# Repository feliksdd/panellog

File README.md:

# PanelLog

PanelLog misst und schaltet den DC-Ertrag eines einzelnen PV-Moduls. Ein Knoten sitzt zwischen Modul und MPPT-Eingang, versorgt sich aus dem Modul und soll seine Daten per Zigbee an BatteryFlex übertragen. Pro Modul wird ein eigener Knoten eingesetzt; verschiedene MPPT-Eingänge bleiben elektrisch getrennt.

## Funktionen

- Modulspannung, Modulstrom sowie daraus berechnete DC-Leistung und Energie.
- Modultemperatur über einen externen Pt1000; lokale Platinentemperatur über NTC.
- Langsame Ein-/Ausschaltung des Modulstroms über einen Low-Side-MOSFET mit Spannungsrückmeldung.
- Optional ein kabelgebundener [POA-Sensor](https://github.com/feliksdd/poa-sensor) zur Einstrahlungsmessung, versorgt über 3,3 V und angeschlossen an einen separaten I²C-Bus.

## Aufbau

| Baugruppe | Ausführung |
|---|---|
| Controller / Funk | ESP32-C6-WROOM-1-N4 |
| Strom und Spannung | INA237AIDGSR, HoVB4026-Vierleiter-Shunt mit 1 mΩ |
| Modulschalter | IPT015N10N5, passiv eingeschaltet, aktiv ausgeschaltet |
| Versorgung | LM5163DDAR, direkt vom Modul auf nominal 3,3 V, bis 500 mA |
| Temperatur | Externer M222 Pt1000 Klasse A; interner 10-kΩ-NTC |
| Mechanik | Vierlagige Platine 118 × 90 × 1,6 mm, Kradex Z74JH ABS |

Der PV-Pluspol ist durchverbunden. Der Rückstrom fließt vom MPPT-Minuspol über Shunt und Q1 zum Modul-Minuspol. Die Elektronik liegt auf Modul-Minus und bleibt bei ausgeschaltetem Q1 versorgt.

Der Spannungsentwurf umfasst ein einzelnes Modul bis 60 V DC; die Versorgung startet typisch bei etwa 9 V. 15 A ist der ursprüngliche Strom-Auslegungspunkt, 20 A ein thermischer Betrachtungsfall. Daraus folgt keine gemessene Dauerstromfreigabe. Kalte Leerlaufspannung und Schaltspitzen der konkreten Modul-/MPPT-Kombination müssen innerhalb der Bauteilgrenzen bleiben. Q1 dient der Ertragsregelung; eine sichere Trennstelle entsteht dadurch nicht.

## Dokumentation

| Inhalt | Datei |
|---|---|
| Schaltungsfunktion und Bauteilwerte | [Schaltung](docs/schaltung.md) |
| Berechnungen, Messbereiche und Genauigkeit | [Auslegung](docs/auslegung.md) |
| Verdrahtung, Montage, Kalibrierung und Betrieb | [Anwendung](docs/anwendung.md) |
| Gehäuse, Lochbild und 3D-Einbindung | [Gehäuse](docs/gehaeuse.md) |
| POA-Kabel und Bestückungsvarianten | [POA-Schnittstelle](docs/poa_schnittstelle.md) |
| KiCad-Projekt und Lagenaufbau | [Hardware](hardware/README.md) |
| Stückliste und Fertigungsunterlagen | [Bestückung](bom/README.md) |
| Pinbelegung und Softwareumfang | [Firmware](firmware/README.md) |
| Vorhandene Gehäuse- und Bauteilmodelle | [3D-Modelle](hardware/3dmodels/README.md) |

Schaltplan und PCB in [hardware/kicad](hardware/kicad/) definieren die Hardware. Das Repository enthält einen POA-Treiberbaustein, aber noch keine vollständige PanelLog-Firmware mit Zigbee-/BatteryFlex-Anbindung.

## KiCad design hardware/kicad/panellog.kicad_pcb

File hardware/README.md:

# Hardware

Das KiCad-10-Projekt liegt in [kicad/panellog.kicad_pro](kicad/panellog.kicad_pro). [Schaltplan](kicad/panellog.kicad_sch) und [PCB](kicad/panellog.kicad_pcb) sind die verbindlichen Konstruktionsdateien. Projektbibliotheken sind über `sym-lib-table` und `fp-lib-table` eingebunden.

| Verzeichnis | Inhalt |
|---|---|
| `kicad/` | Native Schaltung, Layout und Projekteinstellungen |
| `kicad/production/` | Gerber-/Bohrarchiv, BOM, Positionen und IPC-Netzliste |
| `symbols/` | Projektspezifische Symbole |
| `footprints/PanelLog.pretty/` | Projekt-Footprints |
| `3dmodels/` | Bauteil-/Gehäusemodelle und Lizenzen |
| `mechanical/` | Kradex-Gehäusegeometrie |

## Platine

118 × 90 × 1,6 mm, vier Kupferlagen. Der Umriss liegt in KiCad bei X = 81…199 mm und Y = 44,5…134,5 mm. Vorhandene Befestigungslöcher: H1, H3, H4; siehe [Gehäuse und Montage](../docs/gehaeuse.md). Unterteil und Deckel sind als 3D-Modelle an H1 eingebunden.

| Lage | Funktion |
|---|---|
| F.Cu | Bauteile, Versorgung, lokale Signale und Leistungskupfer |
| In1.Cu | GND-Bezug mit getrennten Leistungskupferbereichen |
| In2.Cu | Signalrouting und Leistungskupferbereiche |
| B.Cu | GND und Leistungskupferbereiche |

VDC, MPPT_MINUS, SHUNT_RETURN und GND führen den Modulstrom über getrennte Kupferbereiche mit Durchkontaktierungen. Die Kelvin-Leitungen gehören ausschließlich an die Sense-Anschlüsse des Shunts. Versorgungs-Schaltknoten, Q1-Gate und externe Digitalsignale benötigen Abstand zu diesen Messleitungen. Antennen-, Schrauben- und Spulensperrflächen sind beim Bearbeiten beizubehalten. Kupfergewicht und thermischer Betriebsstrom sind zusätzlich zur Lagenzahl bei der Fertigung festzulegen.

## Bearbeitung und Fertigung

KiCad 10 mit Standardbibliotheken und den lokalen Bibliothekstabellen verwenden. Nach Hardwareänderungen Zonen neu füllen, ERC/DRC mit Schaltplanabgleich ausführen und Fertigungsausgaben neu erzeugen. Die gespeicherten Ausgaben entsprechen keinem automatisch fortgeschriebenen Live-Export.

[Schaltung](../docs/schaltung.md), [Auslegung](../docs/auslegung.md), [Bestückung](../bom/README.md), [3D-Modelle](3dmodels/README.md).

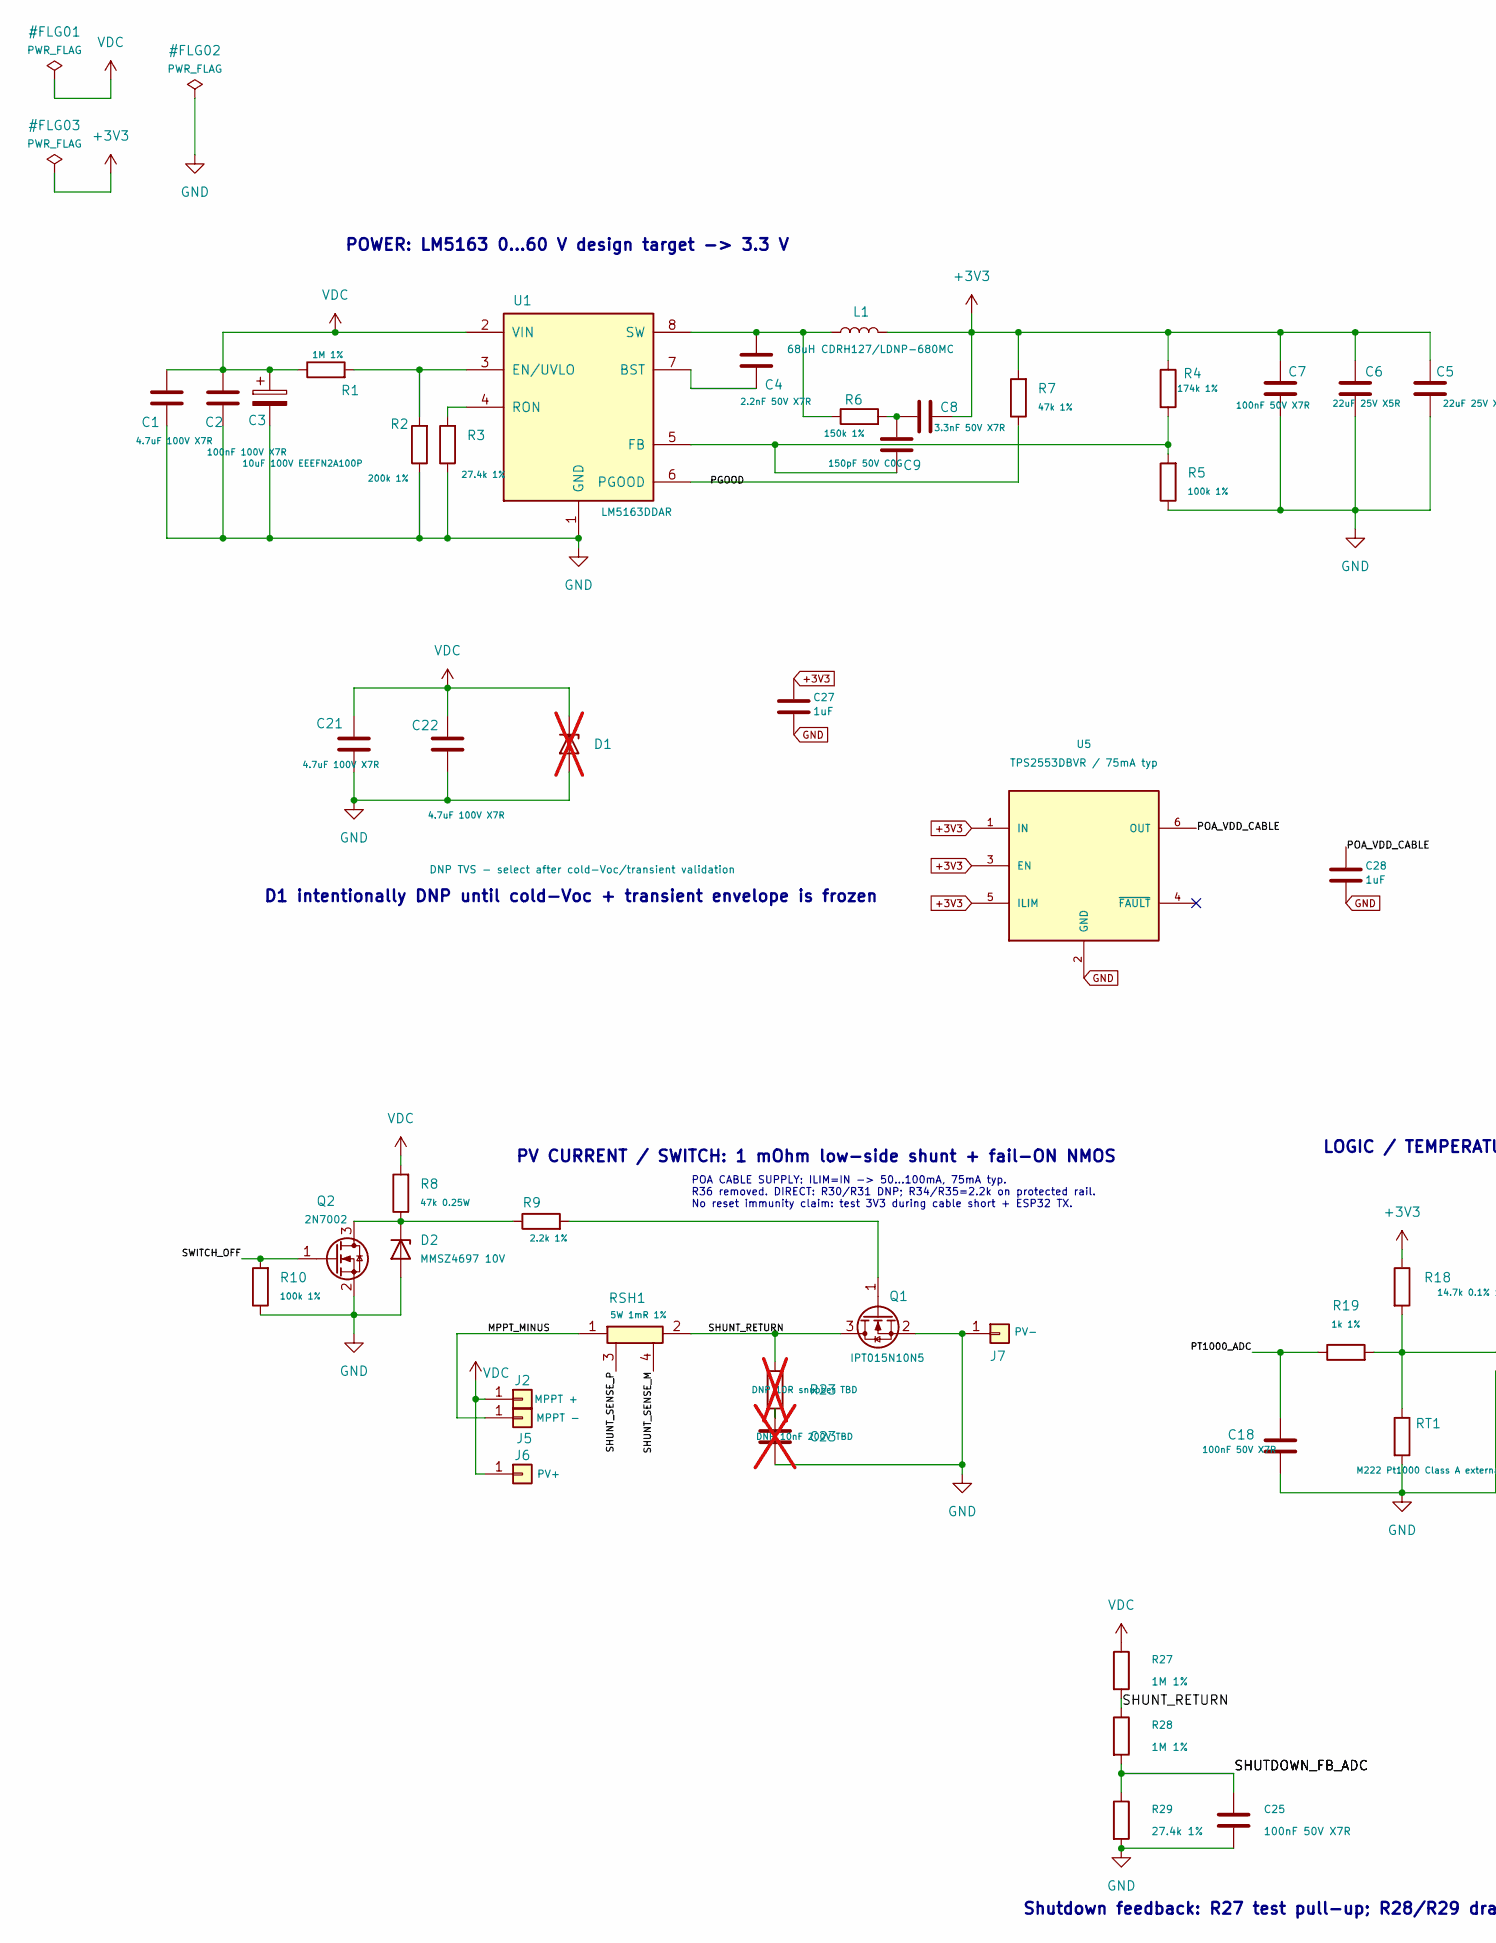
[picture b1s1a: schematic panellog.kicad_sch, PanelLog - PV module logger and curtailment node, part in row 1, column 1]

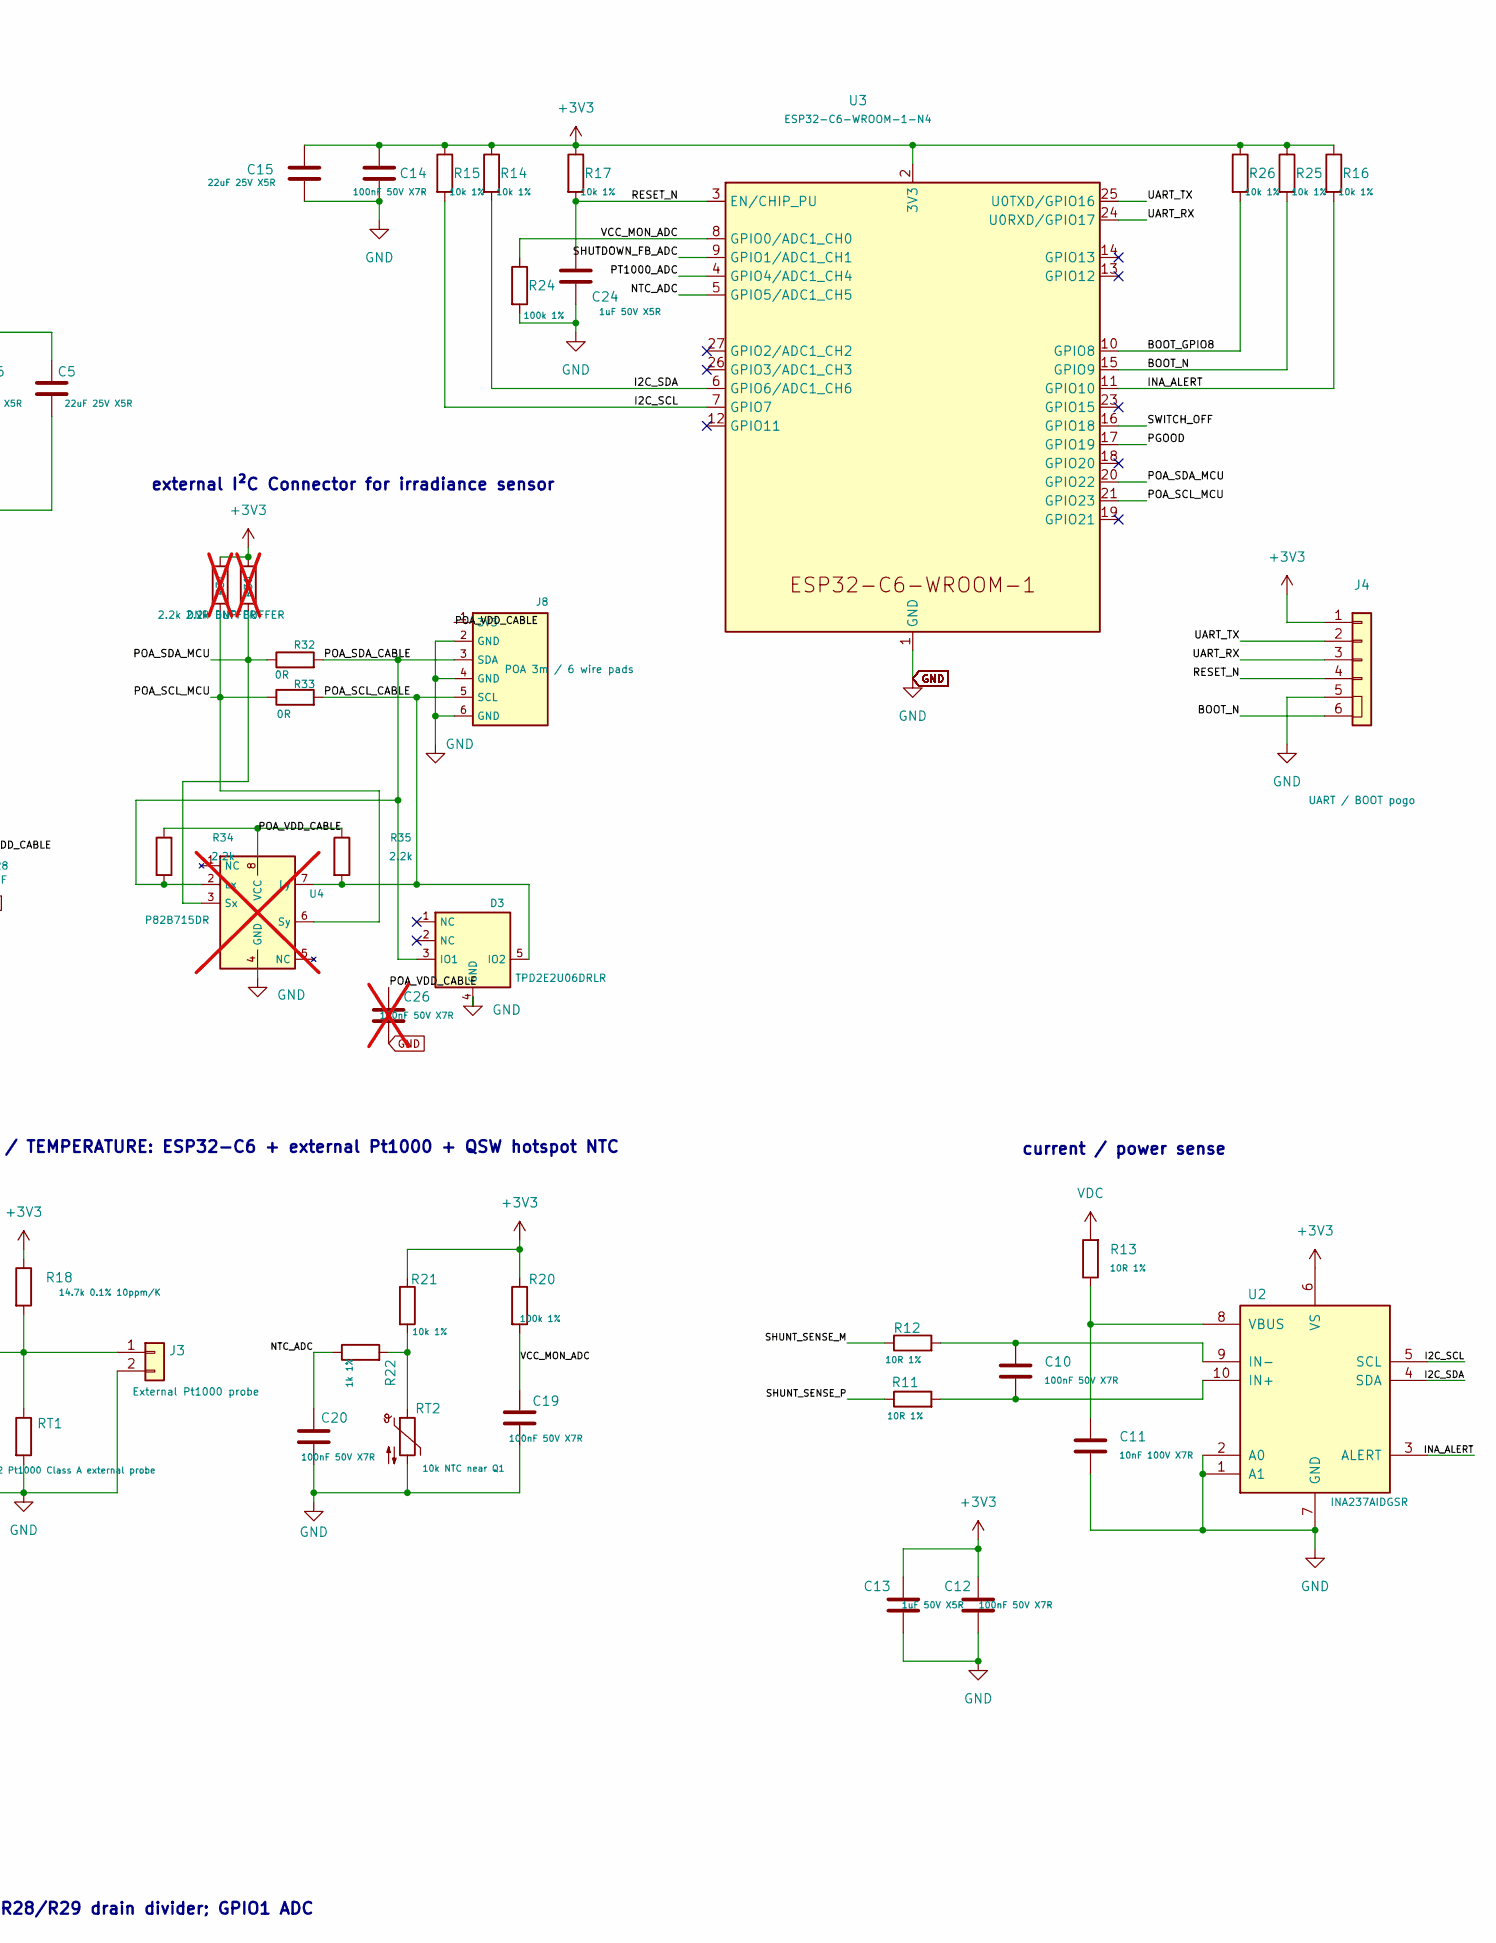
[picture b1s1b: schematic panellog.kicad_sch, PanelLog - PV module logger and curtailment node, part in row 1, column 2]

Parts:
C1, C21, C22: 4.7uF 100V X7R; C_1210_3225Metric; MPN 1210B475K101NT; LCSC C7500895
C2: 100nF 100V X7R; C_0805_2012Metric; MPN CL21B104KCFNNNE; LCSC C28233
C3: 10uF 100V EEEFN2A100P; Panasonic_F_8x10p2; MPN EEEFN2A100P; LCSC C494873
C4: 2.2nF 50V X7R; C_0603_1608Metric; MPN 0603B222K500NT; LCSC C1604
C5, C6, C15: 22uF 25V X5R; C_0805_2012Metric; MPN GRM21BR61E226ME44L; LCSC C86816
C7, C10, C12, C14, C18, C19, C20, C25: 100nF 50V X7R; C_0603_1608Metric; MPN CC0603KRX7R9BB104; LCSC C14663
C8: 3.3nF 50V X7R; C_0603_1608Metric; MPN CL10B332KB8NNNC; LCSC C1613
C9: 150pF 50V C0G; C_0603_1608Metric; MPN CL10C151JB8NNNC; LCSC C37298
C11: 10nF 100V X7R; C_0603_1608Metric; MPN CC0603KRX7R0BB103; LCSC C107059
C13, C24: 1uF 50V X5R; C_0603_1608Metric; MPN CL10A105KB8NNNC; LCSC C15849
C23: DNP 10nF 200V TBD; C_1206_3216Metric; not fitted
C26: 100nF 50V X7R; C_0603_1608Metric; MPN CL10B104KB8NNNC; LCSC C1591; not fitted
C27, C28: 1uF; C_0603_1608Metric; MPN CL10B105KP8NNNC; LCSC C15849
D1: DNP TVS - select after cold-Voc/transient validat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; D_SMB; not fitted
D2: MMSZ4697 10V; D_SOD-123; MPN MMSZ4697; LCSC C2910058
D3: TPD2E2U06DRLR; SOT-553; MPN TPD2E2U06DRLR; LCSC C1972959
J2: MPPT +; PV_MC4_Pigtail_2x2p8_DRAFT
J3: External Pt1000 probe; Pt1000_Cable_2pin_DRAFT
J4: UART / BOOT pogo; UART_BOOT_1x06_Pogo
J5: MPPT -; PV_MC4_Pigtail_2x2p8_DRAFT
J6: PV+; PV_MC4_Pigtail_2x2p8_DRAFT
J7: PV-; PV_MC4_Pigtail_2x2p8_DRAFT
J8: POA 3m / 6 wire pads; POA_Cable_6pad
L1: 68uH CDRH127/LDNP-680MC; Sumida_CDRH127_LD_68uH; MPN CDRH127/LDNP-680MC; LCSC C2452974
Q1: IPT015N10N5; IPT015N10N5_TOLL; MPN 2N7002; LCSC C8545
Q2: 2N7002; SOT-23; MPN 2N7002; LCSC C8545
R1: 1M 1%; R_0603_1608Metric; MPN 0603WAF1004T5E; LCSC C22935
R2: 200k 1%; R_0603_1608Metric; MPN 0603WAF2003T5E; LCSC C25811
R3, R29: 27.4k 1%; R_0603_1608Metric; MPN 0603WAF2742T5E; LCSC C22964
R4: 174k 1%; R_0603_1608Metric; MPN 0603WAF1743T5E; LCSC C22890
R5, R10, R20, R24: 100k 1%; R_0603_1608Metric; MPN 0603WAF1003T5E; LCSC C25803
R6: 150k 1%; R_0603_1608Metric; MPN 0603WAF1503T5E; LCSC C22807
R7: 47k 1%; R_0603_1608Metric; MPN 0603WAF4702T5E; LCSC C25819
R8: 47k 0.25W; R_1206_3216Metric; MPN SCR1206F47K; LCSC C5140109
R9: 2.2k 1%; R_0603_1608Metric; MPN 0603WAF2201T5E; LCSC C4190
R11, R12, R13: 10R 1%; R_0603_1608Metric; MPN 0603WAF100JT5E; LCSC C22859
R14, R15, R16, R17, R21, R25, R26: 10k 1%; R_0603_1608Metric; MPN 0603WAF1002T5E; LCSC C25804
R18: 14.7k 0.1% 10ppm/K; R_0603_1608Metric; MPN PTFR0603B14K7N9; LCSC C19680002
R19, R22: 1k 1%; R_0603_1608Metric; MPN 0603WAF1001T5E; LCSC C21190
R23: DNP 10R snubber TBD; R_1206_3216Metric; not fitted
R27, R28: 1M 1%; R_1206_3216Metric; MPN 1206W4F1004T5E; LCSC C17927
R30, R31: 2.2k DNP BUFFER; R_0603_1608Metric; MPN 0603WAF2201T5E; LCSC C4190; not fitted
R32, R33: 0R; R_0603_1608Metric; MPN 0603WAF0000T5E; LCSC C21189
R34, R35: 2.2k; R_0603_1608Metric; MPN 0603WAF2201T5E; LCSC C4190
RSH1: 5W 1mR 1%; HOVB4026_R001_Kelvin; MPN HOVB4026-5W-1mR-1%; LCSC C481535
RT1: M222 Pt1000 Class A external probe; MPN 32208572; LCSC C17472362
RT2: 10k NTC near Q1; R_0603_1608Metric; MPN NTCG163JF103FT1S; LCSC C406719
U1: LM5163DDAR; LM5164_DDA; MPN LM5163DDAR; LCSC C2873264
U2: INA237AIDGSR; INA237_DGS10; MPN INA237AIDGSR; LCSC C2864837
U3: ESP32-C6-WROOM-1-N4; ESP32_C6_WROOM_1; MPN ESP32-C6-WROOM-1-N4; LCSC C6034714
U4: P82B715DR; SOIC-8_3.9x4.9mm_P1.27mm; MPN P82B715DR; LCSC C2649394; not fitted
U5: TPS2553DBVR / 75mA typ; SOT-23-6; MPN TPS2553DBVR; LCSC C55266

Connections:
/BOOT_GPIO8: R26.2, U3.10 (GPIO8)
/BOOT_N: J4.6, R25.2, U3.15 (GPIO9)
/I2C_SCL: R15.2, U2.5 (SCL), U3.7 (GPIO7)
/I2C_SDA: R14.2, U2.4 (SDA), U3.6 (GPIO6/ADC1_CH6)
/INA_ALERT: R16.2, U2.3 (ALERT), U3.11 (GPIO10)
/MPPT_MINUS: J5.1 (Pin_1_1), RSH1.1
/NTC_ADC: C20.1, R22.1, U3.5 (GPIO5/ADC1_CH5)
/PGOOD: R7.1, U1.6 (PGOOD), U3.17 (GPIO19)
/POA_SCL_CABLE: D3.5 (IO2), J8.5 (SCL), R33.2, R35.2, U4.7 (Ly)
/POA_SCL_MCU: R31.2, R33.1, U3.21 (GPIO23), U4.6 (Sy)
/POA_SDA_CABLE: D3.3 (IO1), J8.3 (SDA), R32.2, R34.2, U4.2 (Lx)
/POA_SDA_MCU: R30.2, R32.1, U3.20 (GPIO22), U4.3 (Sx)
/PT1000_ADC: C18.1, R19.1, U3.4 (GPIO4/ADC1_CH4)
/RESET_N: C24.1, J4.4, R17.2, U3.3 (EN/CHIP_PU)
/SHUNT_RETURN: Q1.3 (D), R23.1, R27.2, R28.1, RSH1.2
/SHUNT_SENSE_M: R12.1, RSH1.4
/SHUNT_SENSE_P: R11.1, RSH1.3
/SHUTDOWN_FB_ADC: C25.1, R28.2, R29.1, U3.9 (GPIO1/ADC1_CH1)
/SWITCH_OFF: Q2.1 (G), R10.2, U3.16 (GPIO18)
/UART_RX: J4.3, U3.24 (U0RXD/GPIO17)
/UART_TX: J4.2, U3.25 (U0TXD/GPIO16)
/VCC_MON_ADC: C19.1, R20.2, R24.1, U3.8 (GPIO0/ADC1_CH0)
GND: C1.2, C2.2, C3.2, C5.2, C6.2, C7.2, C11.1, C12.2, C13.2, C14.1, C15.2, C18.2, C19.2, C20.2, C21.2, C22.2, C23.2, C24.2, C25.2, C26.2, C27.2, C28.2, D1.2 (A), D2.2 (A), D3.4 (GND), J3.2, J4.5, J7.1 (Pin_1_1), J8.2 (GND), J8.4 (GND), J8.6 (GND), Q1.2 (S), Q2.2 (S), R2.1, R3.1, R5.1, R10.1, R24.2, R29.2, RT1.2, RT2.2, U1.1 (GND), U1.9 (EP), U2.1 (A1), U2.2 (A0), U2.7 (GND), U3.1 (GND), U3.28 (GND), U3.29 (GND), U4.4 (GND), U5.2 (GND)
unnamed: C8.2, C9.1, R6.2
unnamed: C23.1, R23.2
unnamed: C27.1, U5.1 (IN), U5.3 (EN), U5.5 (ILIM)
unnamed: D2.1 (K), Q2.3 (D), R8.1, R9.1
unnamed: J3.1, R18.2, R19.2, RT1.1
unnamed: Q1.1 (G), R9.2
unnamed: R21.2, R22.2, RT2.1
unnamed: C4.1, U1.7 (BST)
unnamed: R1.2, R2.2, U1.3 (EN/UVLO)
unnamed: C9.2, R4.2, R5.2, U1.5 (FB)
unnamed: R3.2, U1.4 (RON)
unnamed: C4.2, L1.1, R6.1, U1.8 (SW)
unnamed: C10.1, R11.2, U2.10 (IN+)
unnamed: C10.2, R12.2, U2.9 (IN-)
unnamed: C11.2, R13.1, U2.8 (VBUS)
VDC: C1.1, C2.1, C3.1, C21.1, C22.1, D1.1 (K), J2.1 (Pin_1_1), J6.1 (Pin_1_1), R1.1, R8.2, R13.2, R27.1, U1.2 (VIN)

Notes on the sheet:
POWER: LM5163 0...60 V design target -> 3.3 V
PV CURRENT / SWITCH: 1 mOhm low-side shunt + fail-ON NMOS
LOGIC / TEMPERATURE: ESP32-C6 + external Pt1000 + QSW hotspot NTC
D1 intentionally DNP until cold-Voc + transient envelope is frozen
Shutdown feedback: R27 test pull-up; R28/R29 drain divider; GPIO1 ADC
external I²C Connector for irradiance sensor
current / power sense
POA CABLE SUPPLY: ILIM=IN -> 50...100mA, 75mA typ. R36 removed. DIRECT: R30/R31 DNP; R34/R35=2.2k on protected rail. No reset immunity claim: test 3V3 during cable short + ESP32 TX.

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
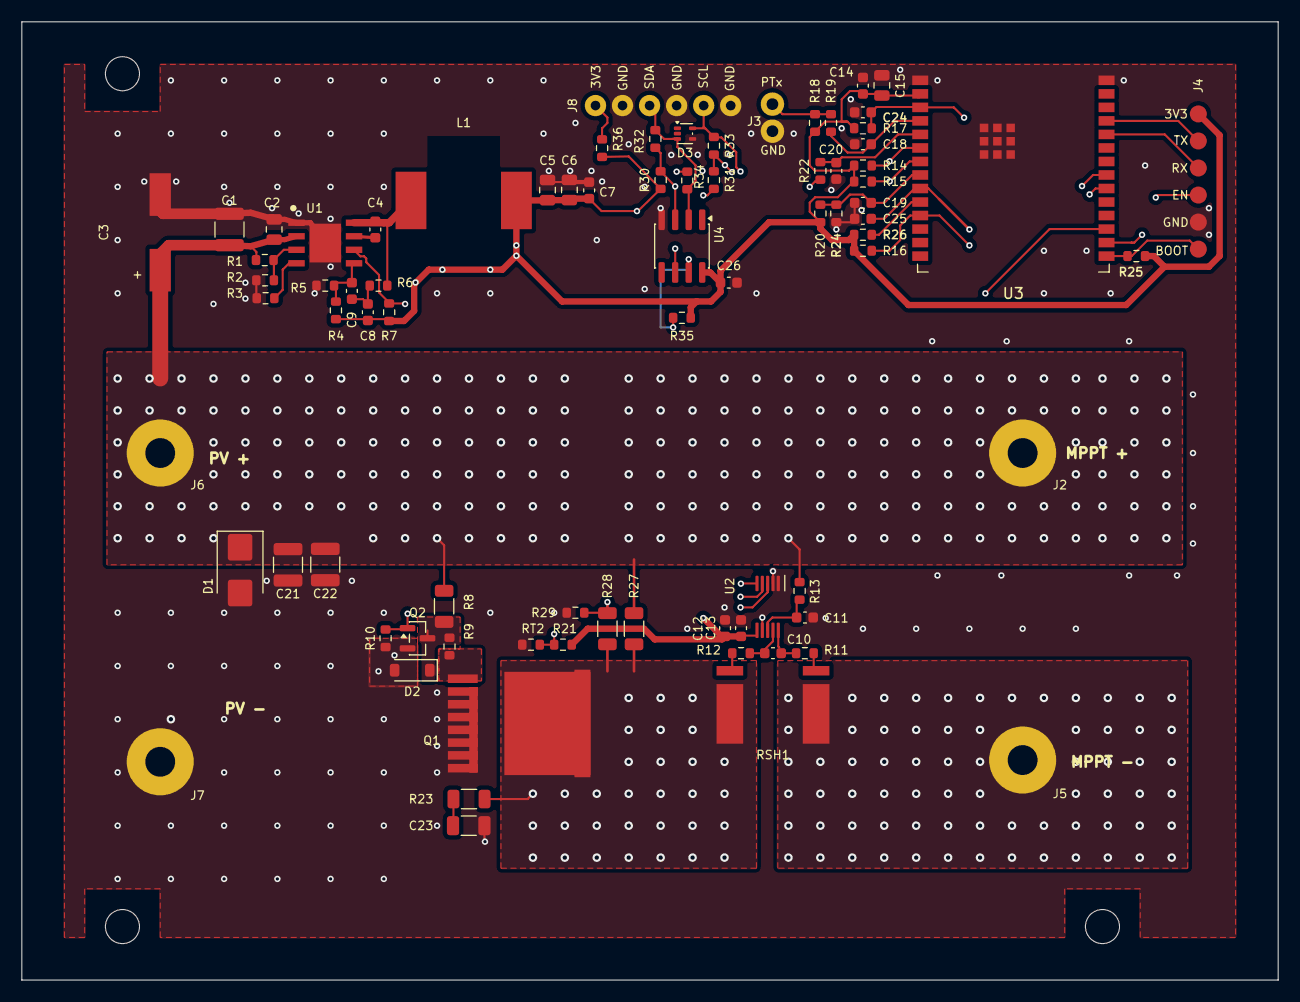
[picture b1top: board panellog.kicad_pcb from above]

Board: 4 copper layers, 118.0 x 90.0 mm, 82 parts (0 on the bottom side), 40 nets.

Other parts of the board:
H1, H3, H4: MountingHole_3p2_Nylon
R36: 0R; R_0603_1608Metric

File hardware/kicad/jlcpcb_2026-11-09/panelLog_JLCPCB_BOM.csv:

"Comment","Designator","Footprint","LCSC Part #"
"4.7uF 100V X7R","C1, C21, C22","Capacitor_SMD:C_1210_3225Metric","C7500895"
"100nF 100V X7R","C2","Capacitor_SMD:C_0805_2012Metric","C28233"
"10uF 100V EEEFN2A100P","C3","PanelLog:Panasonic_F_8x10p2","C494873"
"2.2nF 50V X7R","C4","Capacitor_SMD:C_0603_1608Metric","C1604"
"22uF 25V X5R","C5, C6, C15","Capacitor_SMD:C_0805_2012Metric","C86816"
"100nF 50V X7R","C7, C10, C12, C14, C18, C19, C20, C25","Capacitor_SMD:C_0603_1608Metric","C14663"
"3.3nF 50V X7R","C8","Capacitor_SMD:C_0603_1608Metric","C1613"
"150pF 50V C0G","C9","Capacitor_SMD:C_0603_1608Metric","C37298"
"10nF 100V X7R","C11","Capacitor_SMD:C_0603_1608Metric","C107059"
"1uF 50V X5R","C13, C24","Capacitor_SMD:C_0603_1608Metric","C15849"
"MMSZ4697 10V C2910058","D2","Diode_SMD:D_SOD-123","C2910058"
"TPD2E2U06DRLR","D3","Package_TO_SOT_SMD:SOT-553","C1972959"
"68uH CDRH127/LDNP-680MC","L1","PanelLog:Sumida_CDRH127_LD_68uH","C2452974"
"IPT015N10N5","Q1","PanelLog:IPT015N10N5_TOLL","C108964"
"2N7002","Q2","Package_TO_SOT_SMD:SOT-23","C8545"
"1M 1%","R1","Resistor_SMD:R_0603_1608Metric","C22935"
"200k 1%","R2","Resistor_SMD:R_0603_1608Metric","C25811"
"27.4k 1%","R3, R29","Resistor_SMD:R_0603_1608Metric","C22964"
"174k 1%","R4","Resistor_SMD:R_0603_1608Metric","C22890"
"100k 1%","R5, R10, R20, R24","Resistor_SMD:R_0603_1608Metric","C25803"
"150k 1%","R6","Resistor_SMD:R_0603_1608Metric","C22807"
"47k 1%","R7","Resistor_SMD:R_0603_1608Metric","C25819"
"47k 0.25W","R8","Resistor_SMD:R_1206_3216Metric","C5140109"
"2.2k 1%","R9","Resistor_SMD:R_0603_1608Metric","C4190"
"10R 1%","R11, R12, R13","Resistor_SMD:R_0603_1608Metric","C22859"
"10k 1%","R14, R15, R16, R17, R21, R25, R26","Resistor_SMD:R_0603_1608Metric","C25804"
"14.7k 0.1% 10ppm/K","R18","Resistor_SMD:R_0603_1608Metric","C19680002"
"1k 1%","R19, R22","Resistor_SMD:R_0603_1608Metric","C21190"
"1M 1%","R27, R28","Resistor_SMD:R_1206_3216Metric","C17927"
"2.2k","R30, R31","Resistor_SMD:R_0603_1608Metric","C4190"
"0R","R32, R33, R36","Resistor_SMD:R_0603_1608Metric","C21189"
"HOVB4026-5W-1mR-1%","RSH1","PanelLog:HOVB4026_R001_Kelvin","C481535"
"10k NTC near Q1","RT2","Resistor_SMD:R_0603_1608Metric","C406719"
"LM5163DDAR","U1","PanelLog:LM5164_DDA","C2873264"
"INA237AIDGSR","U2","PanelLog:INA237_DGS10","C2864837"
"ESP32-C6-MINI-1-N4","U3","PanelLog:ESP32_C6_MINI_1","C5736265"

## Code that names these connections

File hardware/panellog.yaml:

libraries:
  - symbols/panellog.kicad_sym

config:
  page_size: A3
  title: "PanelLog PV module logger and curtailment node"
  rev: "0.1"
  designer: "feliksdd"
  grid: 50
  strict_erc: false
  pcb_sheet_spacing: 25

power_nets:
  - GND
  - PV_PLUS
  - VCC_3V3

parts:
  "INA228AIDGSR": { mpn: "INA228AIDGSR", manufacturer: "Texas Instruments" }
  "LM5164DDAR": { mpn: "LM5164DDAR", manufacturer: "Texas Instruments" }
  "IPT015N10N5": { mpn: "IPT015N10N5", manufacturer: "Infineon" }
  "BVB-M-R0007-1.0 0.7mR": { mpn: "BVB-M-R0007-1.0", manufacturer: "Isabellenhuette" }
  "E73-2G4M08S1C": { mpn: "E73-2G4M08S1C", manufacturer: "Ebyte" }
  "M222 Pt1000 Class A external probe": { mpn: "32208572", manufacturer: "YAGEO Nexensos" }

sheets:
  power:
    components:
      - ref: U1
        symbol: PanelLog:LM5164DDAR
        value: "LM5164DDAR"
        pins: { "1": GND, "2": PV_PLUS, "3": UVLO, "4": RON, "5": FB, "6": PGOOD, "7": BST, "8": SW }

      - { ref: C1, symbol: PanelLog:C, value: "2.2uF 100V X7R", pins: { "1": PV_PLUS, "2": GND }, host: U1.2 }
      - { ref: C2, symbol: PanelLog:C, value: "100nF 100V X7R", pins: { "1": PV_PLUS, "2": GND }, host: U1.2 }
      - { ref: C3, symbol: PanelLog:C, value: "10uF 100V bulk/damping", pins: { "1": PV_PLUS, "2": GND } }

      - { ref: R1, symbol: PanelLog:R, value: "1.0M 1%", pins: { "1": PV_PLUS, "2": UVLO } }
      - { ref: R2, symbol: PanelLog:R, value: "200k 1%", pins: { "1": UVLO, "2": GND } }
      - { ref: R3, symbol: PanelLog:R, value: "27.4k 1%", pins: { "1": RON, "2": GND } }

      - { ref: C4, symbol: PanelLog:C, value: "2.2nF 50V X7R", pins: { "1": BST, "2": SW }, host: U1.7 }
      - { ref: L1, symbol: PanelLog:L, value: "68uH Isat>=1.8A", pins: { "1": SW, "2": VCC_3V3 } }

      - { ref: C5, symbol: PanelLog:C, value: "22uF 10V X7R", pins: { "1": VCC_3V3, "2": GND } }
      - { ref: C6, symbol: PanelLog:C, value: "22uF 10V X7R", pins: { "1": VCC_3V3, "2": GND } }
      - { ref: C7, symbol: PanelLog:C, value: "100nF 10V X7R", pins: { "1": VCC_3V3, "2": GND } }

      - { ref: R4, symbol: PanelLog:R, value: "175k 0.1%", pins: { "1": VCC_3V3, "2": FB } }
      - { ref: R5, symbol: PanelLog:R, value: "100k 0.1%", pins: { "1": FB, "2": GND } }

      - { ref: R6, symbol: PanelLog:R, value: "150k 1%", pins: { "1": SW, "2": RIPPLE } }
      - { ref: C8, symbol: PanelLog:C, value: "3.3nF X7R", pins: { "1": RIPPLE, "2": VCC_3V3 } }
      - { ref: C9, symbol: PanelLog:C, value: "150pF C0G", pins: { "1": RIPPLE, "2": FB } }

      - { ref: R7, symbol: PanelLog:R, value: "47k", pins: { "1": VCC_3V3, "2": PGOOD } }
      - { ref: D1, symbol: PanelLog:Zener, value: "DNP - TVS after cold-Voc/transient validation", dnp: true, pins: { "1": PV_PLUS, "2": GND } }

  measurement_switch:
    components:
      - { ref: J1, symbol: PanelLog:Conn_01x02, value: "PV MODULE IN / PV-rated pigtail", pins: { "1": PV_PLUS, "2": GND } }
      - { ref: J2, symbol: PanelLog:Conn_01x02, value: "MPPT OUT / PV-rated pigtail", pins: { "1": PV_PLUS, "2": MPPT_MINUS } }

      - { ref: RSH1, symbol: PanelLog:BVB_R0007, value: "BVB-M-R0007-1.0 0.7mR", pins: { "1": MPPT_MINUS, "2": SHUNT_RETURN } }

      - ref: Q1
        symbol: PanelLog:IPT015N10N5
        value: "IPT015N10N5"
        pins:
          bulk:
            GND: ["2","3","4","5","6","7","8"]
          named:
            "1": QSW_GATE
            "9": SHUNT_RETURN

      - { ref: R8, symbol: PanelLog:R, value: "220k 0.25W", pins: { "1": PV_PLUS, "2": QSW_GATE_BIAS } }
      - { ref: D2, symbol: PanelLog:Zener, value: "10V VGS clamp", pins: { "1": QSW_GATE_BIAS, "2": GND } }
      - { ref: R9, symbol: PanelLog:R, value: "100R", pins: { "1": QSW_GATE_BIAS, "2": QSW_GATE } }

      - { ref: Q2, symbol: PanelLog:NMOS, value: "2N7002", pins: { "1": SWITCH_OFF, "2": GND, "3": QSW_GATE_BIAS } }
      - { ref: R10, symbol: PanelLog:R, value: "100k", pins: { "1": SWITCH_OFF, "2": GND } }

      - ref: U2
        symbol: PanelLog:INA228AIDGSR
        value: "INA228AIDGSR"
        pins:
          "1": GND
          "2": GND
          "3": INA_ALERT
          "4": I2C_SDA
          "5": I2C_SCL
          "6": VCC_3V3
          "7": GND
          "8": VBUS_SENSE
          "9": INA_INM
          "10": INA_INP

      - { ref: R11, symbol: PanelLog:R, value: "10R", pins: { "1": MPPT_MINUS, "2": INA_INP } }
      - { ref: R12, symbol: PanelLog:R, value: "10R", pins: { "1": SHUNT_RETURN, "2": INA_INM } }
      - { ref: C10, symbol: PanelLog:C, value: "100nF C0G/X7R", pins: { "1": INA_INP, "2": INA_INM } }

      - { ref: R13, symbol: PanelLog:R, value: "10R", pins: { "1": PV_PLUS, "2": VBUS_SENSE } }
      - { ref: C11, symbol: PanelLog:C, value: "10nF 100V", pins: { "1": VBUS_SENSE, "2": GND } }

      - { ref: C12, symbol: PanelLog:C, value: "100nF", pins: { "1": VCC_3V3, "2": GND }, host: U2.6 }
      - { ref: C13, symbol: PanelLog:C, value: "1uF", pins: { "1": VCC_3V3, "2": GND }, host: U2.6 }

  logic_temperature:
    components:
      - ref: U3
        symbol: PanelLog:E73-2G4M08S1C
        value: "E73-2G4M08S1C"
        pins:
          bulk:
            VCC_3V3: ["19","23"]
            GND: ["5","21","24"]
          named:
            "3": PT1000_ADC
            "4": VCC_MON_ADC
            "7": NTC_ADC
            "11": XL1
            "12": I2C_SDA
            "13": XL2
            "14": I2C_SCL
            "16": SWITCH_OFF
            "20": PGOOD
            "22": INA_ALERT
            "26": RESET_N
            "37": SWDIO
            "39": SWDCLK

      - { ref: C14, symbol: PanelLog:C, value: "100nF", pins: { "1": VCC_3V3, "2": GND }, host: U3.19 }
      - { ref: C15, symbol: PanelLog:C, value: "4.7uF", pins: { "1": VCC_3V3, "2": GND }, host: U3.19 }

      - { ref: R14, symbol: PanelLog:R, value: "10k", pins: { "1": VCC_3V3, "2": I2C_SDA } }
      - { ref: R15, symbol: PanelLog:R, value: "10k", pins: { "1": VCC_3V3, "2": I2C_SCL } }
      - { ref: R16, symbol: PanelLog:R, value: "10k", pins: { "1": VCC_3V3, "2": INA_ALERT } }
      - { ref: R17, symbol: PanelLog:R, value: "10k", pins: { "1": VCC_3V3, "2": RESET_N } }

      - { ref: Y1, symbol: PanelLog:Crystal, value: "32.768kHz CL=12.5pF", pins: { "1": XL1, "2": XL2 } }
      - { ref: C16, symbol: PanelLog:C, value: "22pF C0G", pins: { "1": XL1, "2": GND } }
      - { ref: C17, symbol: PanelLog:C, value: "22pF C0G", pins: { "1": XL2, "2": GND } }

      - { ref: J3, symbol: PanelLog:Conn_01x02, value: "External Pt1000 probe", pins: { "1": PT1000_RAW, "2": GND } }
      - { ref: RT1, symbol: PanelLog:Pt1000, value: "M222 Pt1000 Class A external probe", pins: { "1": PT1000_RAW, "2": GND } }
      - { ref: R18, symbol: PanelLog:R, value: "14.7k 0.05% 10ppm/K", pins: { "1": VCC_3V3, "2": PT1000_RAW } }
      - { ref: R19, symbol: PanelLog:R, value: "1k", pins: { "1": PT1000_RAW, "2": PT1000_ADC } }
      - { ref: C18, symbol: PanelLog:C, value: "100nF", pins: { "1": PT1000_ADC, "2": GND } }

      - { ref: R20, symbol: PanelLog:R, value: "1k", pins: { "1": VCC_3V3, "2": VCC_MON_ADC } }
      - { ref: C19, symbol: PanelLog:C, value: "100nF", pins: { "1": VCC_MON_ADC, "2": GND } }

      - { ref: R21, symbol: PanelLog:R, value: "10k 1%", pins: { "1": VCC_3V3, "2": NTC_RAW } }
      - { ref: RT2, symbol: PanelLog:NTC, value: "10k NTC near Q1", pins: { "1": NTC_RAW, "2": GND } }
      - { ref: R22, symbol: PanelLog:R, value: "1k", pins: { "1": NTC_RAW, "2": NTC_ADC } }
      - { ref: C20, symbol: PanelLog:C, value: "100nF", pins: { "1": NTC_ADC, "2": GND } }

      - ref: J4
        symbol: PanelLog:Conn_01x05
        value: "SWD pogo"
        pins: { "1": VCC_3V3, "2": SWDIO, "3": SWDCLK, "4": RESET_N, "5": GND }

root:
  instantiate:
    - { sheet: power }
    - { sheet: measurement_switch }
    - { sheet: logic_temperature }
